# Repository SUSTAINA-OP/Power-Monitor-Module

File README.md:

<html lang="en">

<head>
	<meta charset="uft-8">
	<meta name="author" content="Masato Kubotera">
    <meta name="description" content="">
</head>

<body>
    <p><strong>This product is currently under development!</strong></p>
	<h1>Power Monitor Module</h1>
        <p>
            This product is a high-side sensing current/voltage monitor module. The sensing voltage is 0~36V and the current is ±20A. The operating voltage is 2.7~5.5V, and these values are available via I<sup>2</sup>C I/F. The slave address is selectable on the board, and up to 16 modules in total are connected.<br>
            <br>
            This product has been verified to be able to acquire current and voltage values using the following Arduino library.
            <ul>
                <li><a href="https://github.com/asukiaaa/INA226_asukiaaa">asukiaaa/INA226_asukiaaa</a></li>
            </ul>
            SUSTAINA-OP<sup>TM</sup> connects to Jetson Xavier NX through a carrier board and obtains values using the following library.
            <ul>
                <li><a href="https://github.com/hiroki-0001/INA226_Library">hiroki-0001/INA226_Library</a></li>
            </ul>
        </p>
	<h2>Features Rev. 2</h2>
        <p>
            <table>
                <tr>
                    <th>Top Surface of PCB</th>
                    <th>Bottom Surface of PCB</th>
                    <th>Assembled Electronic Components</th>
                </tr>
                <tr>
                    <td></td>
                    <td></td>
                    <td></td>
                </tr>
            </table>
        </p>
    <h3>PCB</h3>
        <p>
            <ul>
                <li>8" x 5" (20.32mm x 12.7mm) PCB layout</li>
                <li>1" (2.54mm) pitch through-holes for pin headers
                    <ul>
                        <li>2 x 5 pin headers - 1
                            <ul>
                                <li><strong>VIN+</strong>: Power input side</li>
                            </ul>
                        </li>
                        <li>2 x 5 pin headers - 2
                            <ul>
                                <li><strong>VIN-</strong>: Load side</li>
                            </ul>
                        </li>
                        <li>1 x 4 pin headers: I<sup>2</sup>C Interface
                            <ul>
                                <li><strong>SDA</strong>: Serial bus data line</li>
                                <li><strong>SCL</strong>: Serial bus clock line</li>
                                <li><strong>VS</strong>: Supply voltage</li>
                                <li><strong>GND</strong>: Common Ground</li>
                            </ul>
                        </li>
                    </ul>
                </li>
            </ul>
            
        </p>
    <h3><a href="https://www.ti.com/product/en-us/INA226">Texas Instruments INA226</a></h3>
        <p>
            <ul>
                <li>Bus voltage sensing from 0 V to 36 V</li>
                <li>Power-supply operation: 2.7 V to 5.5 V</li>
                <li>High accuracy:
                    <ul>
                        <li>Gain error: 0.1% (maximum)</li>
                        <li>Offset: 10 μV (maximum)</li>
                    </ul>
                </li>
            </ul>
            Note: The I<sup>2</sup>C address of this product is selectable from 16 addresses by the short lands on the board.
        <p>
	<h2>Development Environments</h2>
    <p>
        This product is designed with the following software.
            <ul>
                <li><a href="https://www.autodesk.com/products/eagle/overview">Autodesk Eagle 9.6.2</a></li>
            </ul>
    </p>
    <h2>Repository Contents</h2>
        <p>
            <dl>
                <dt><a href="/images">\images</a></dt>
                <dd>PCB preview images and capture of design screen</dd>
                <dt><a href="/libraries">\libraries</a></dt>
                <dd>Libraries used in Autodesk Eagle design</dd>
                <dt><a href="/pcb_order">\pcb_order</a> </dt>
                <dd>Gerber data and documentation for ordering PCB</dd>
                <dt><a href="/schematic.pdf">schematic.pdf</a></dt>
                <dd>Circuit diagram of this product</dd>
                <dt>*.brd</dt>
                <dd>Board wiring design file by Autodesk Eagle</dd>
                <dt>*.sch</dt>
                <dd>Circuit diagram design file by Autodesk Eagle</dd>
                <dt><a href="/.gitignore">.gitignore</a></dt>
                <dd>A file that tells Git not to track a particular file</dd>            <dt><a href="/LICENSE">LICENSE</a></dt>
                <dd>License to use this product</dd>
            </dl>
        </p>
    <h2>Documentation</h2>
        <p>
            The following documents are available for this product.
            <ul>
                <li><a href="/pcb_order/README.md">\pcb_order\README.md</a>: Information for ordering the PCB or PCBA</li>
            </ul>
        </p>
    <h2>References</h2>
        <p>
            This product was designed with reference to the following products.
            <ul>
                <li><a href="https://www.ti.com/tool/ja-jp/INA226EVM">Texas Instruments INA226EVM: INA226 evaluation module</a></li>
                <li><a href="https://strawberry-linux.com/catalog/items?code=12031">Strawberry Linux INA226: I2C digital current, voltage, and power meter module (up to 20A)</a></li>
            </ul>
        </p>
    <h2>Contact</h2>
        <p>
            If you have any questions, please contact the designer of this product, Masato Kubodera, by <a href="mailto:masato.kubotera@sustaina-op.com">e-mail</a>.<br>
            E-mail: <a href="mailto:masato.kubotera@sustaina-op.com">masato.kubotera@sustaina-op.com</a>
        </p>
    <h2>License Information</h2>
        <p>
            This product is open source. Please review the <a href="/LICENSE">LICENSE</a> for license information.<br>
            <br>
            This product by Masato Kubotera is licensed under a <a href="http://creativecommons.org/licenses/by-nc-sa/4.0/">Creative Commons Attribution-NonCommercial-ShareAlike 4.0 International License</a>.
        </p>
</body>
</html>

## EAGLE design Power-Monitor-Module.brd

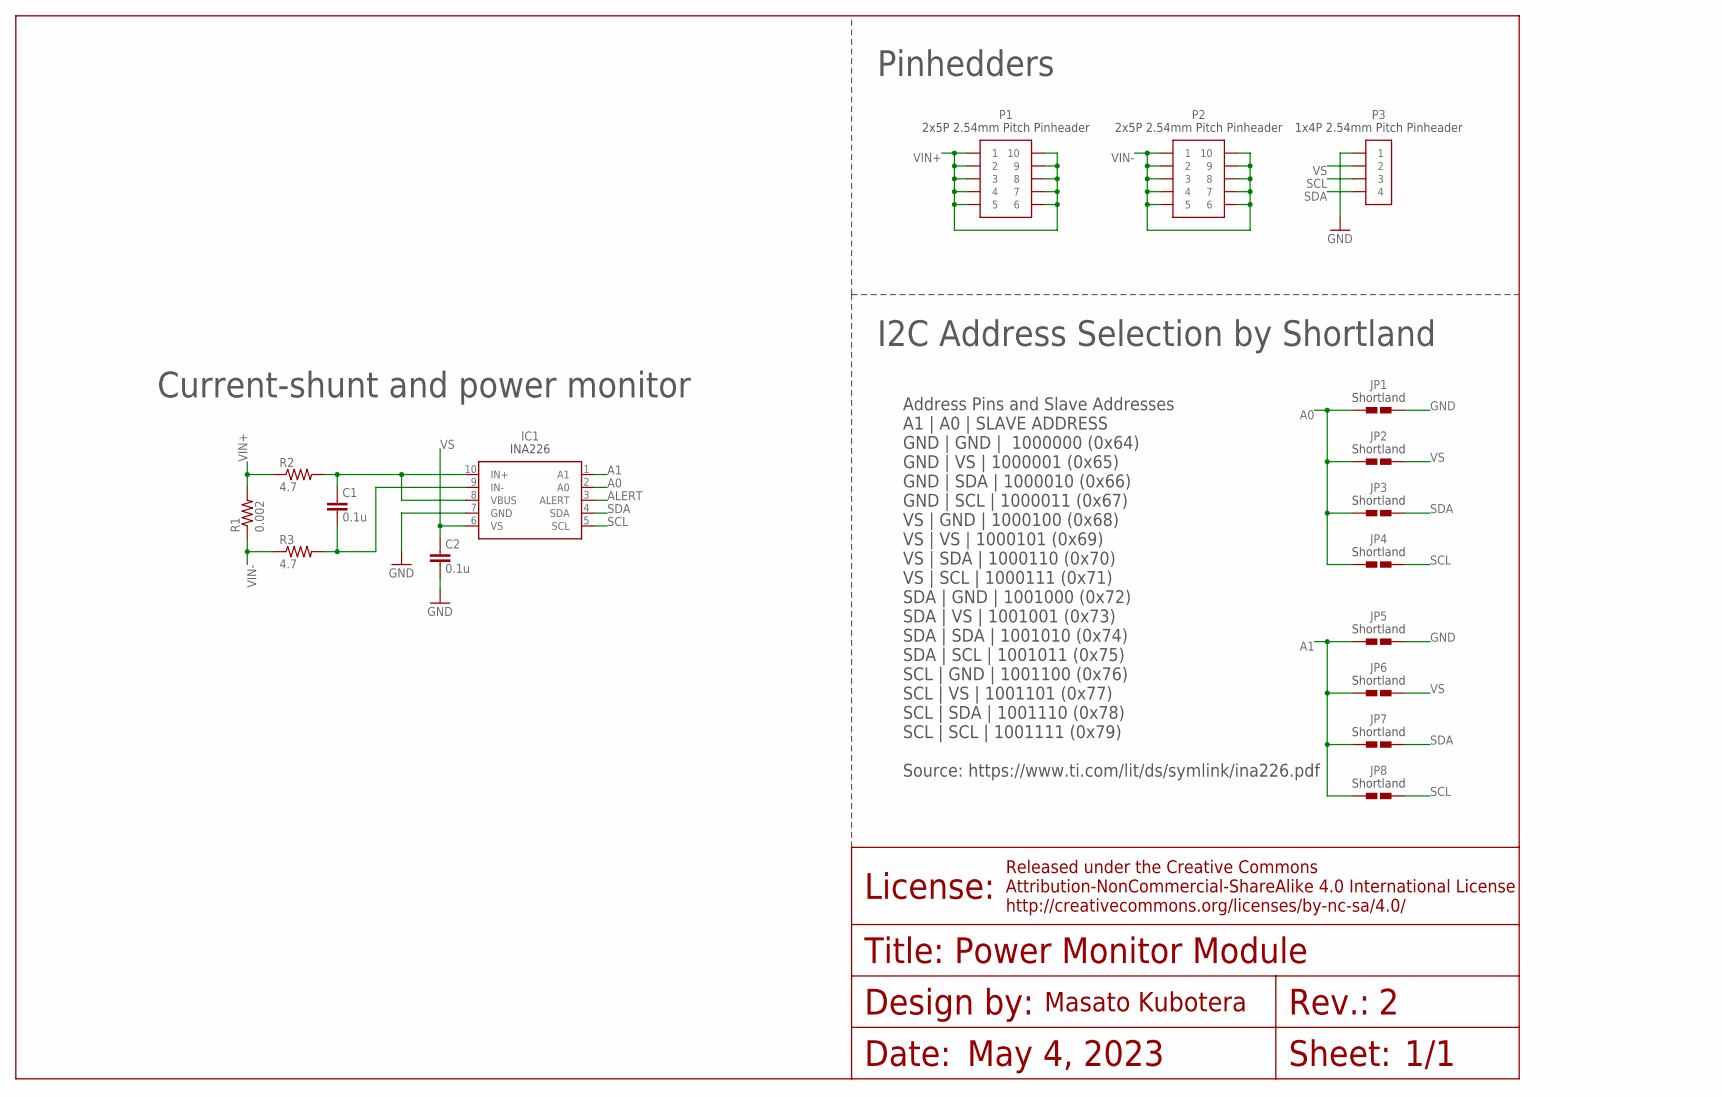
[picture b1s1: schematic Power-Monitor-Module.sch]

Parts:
C1, C2: 0.1u; C0402
IC1: INA226; MSOP-10
JP1, JP2, JP3, JP4, JP5, JP6, JP7, JP8: SHORTLAND
P1, P2: 2X5P
P3: 1X4P
R1: 0.002; R2512
R2, R3: 4.7; R0402

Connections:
A0: IC1.2 (A0), JP1.1, JP2.1, JP3.1, JP4.1
A1: IC1.1 (A1), JP5.1, JP6.1, JP7.1, JP8.1
ALERT: IC1.3 (ALERT)
GND: C2.2, IC1.7 (GND), JP1.2, JP5.2, P3.1
IN+: C1.1, IC1.8 (VBUS), IC1.10 (IN+), R2.2
IN-: C1.2, IC1.9 (IN-), R3.2
SCL: IC1.5 (SCL), JP4.2, JP8.2, P3.3
SDA: IC1.4 (SDA), JP3.2, JP7.2, P3.4
VIN+: P1.1, P1.2, P1.3, P1.4, P1.5, P1.6, P1.7, P1.8, P1.9, P1.10, R1.2, R2.1
VIN-: P2.1, P2.2, P2.3, P2.4, P2.5, P2.6, P2.7, P2.8, P2.9, P2.10, R1.1, R3.1
VS: C2.1, IC1.6 (VS), JP2.2, JP6.2, P3.2

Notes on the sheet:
I2C Address Selection by Shortland
Pinhedders
Current-shunt and power monitor
May 4, 2023
Power Monitor Module
1/1
Address Pins and Slave Addresses A1 | A0 | SLAVE ADDRESS GND | GND | 1000000 (0x64) GND | VS | 1000001 (0x65) GND | SDA | 1000010 (0x66) GND | SCL | 1000011 (0x67) VS | GND | 1000100 (0x68) VS | VS | 1000101 (0x69) VS | SDA | 1000110 (0x70) VS | SCL | 1000111 (0x71) SDA | GND | 1001000 (0x72) SDA |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

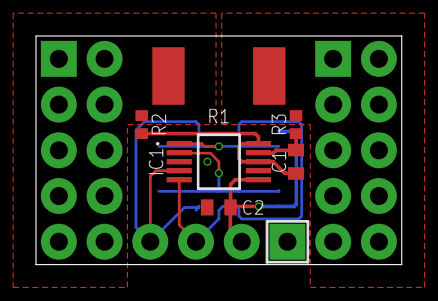
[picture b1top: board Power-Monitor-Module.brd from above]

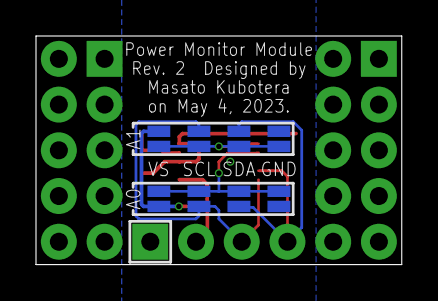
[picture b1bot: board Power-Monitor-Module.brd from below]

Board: 2 copper layers, 20.3 x 12.7 mm, 17 parts (8 on the bottom side), 10 nets.

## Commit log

2023-04-23 Initial Upload
2023-04-28 Add information on ordering PCB or PCBA to READEME
2023-06-13 Made Rev.2 with the measurement IC changed to INA226.
2023-06-14 Changed the color of the board preview to a shade closer to the actual color.

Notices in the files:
parts and their libraries:
Frames: Released under the Creative Commons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
